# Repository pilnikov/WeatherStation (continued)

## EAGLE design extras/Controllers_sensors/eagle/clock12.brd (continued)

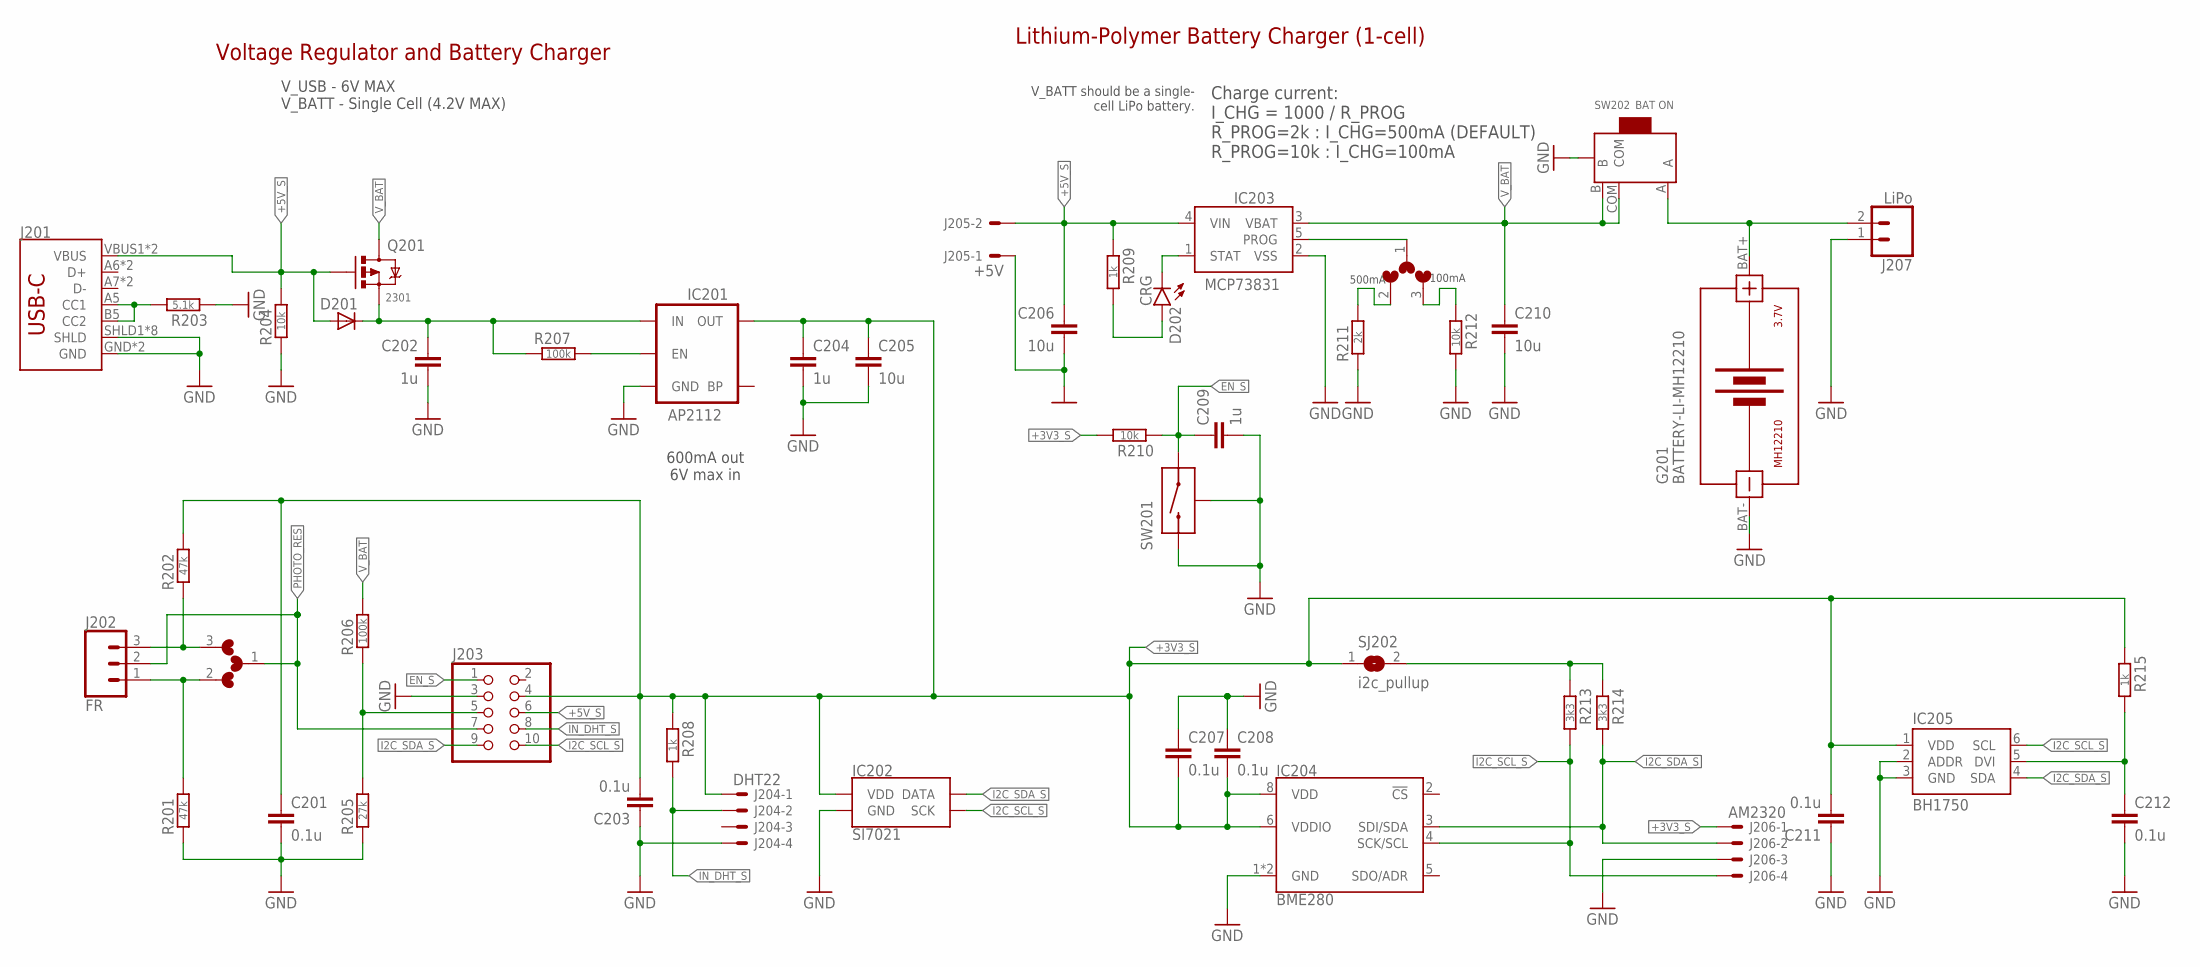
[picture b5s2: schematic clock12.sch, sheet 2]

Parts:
C201, C203, C207, C208, C211, C212: 0.1u; 0603-CAP
C202, C204, C209: 1u; 0603-CAP
C205, C206, C210: 10u; 0603-CAP
D201: 1N5819; SOD123
D202: CRG; LED-0603
G201: BATTERY-LI-MH12210
IC201: AP2112; SOT23-5
IC202: SI7021; DFN-6-3X3-SI7021
IC203: MCP73831; SOT23-5
IC204: BME280; LGA-8-2.5X2.5
IC205: BH1750; WSOF6L
J201: USB_C16PIN; USB-C-16P
J202: FR; 1X03
J203: HEADER-2X5; 2X05
J204: DHT22; 70543-04
J205: +5V; 70543-02
J206: AM2320; 70543-04
J207: LiPo; JST-2-SMD
Q201: 2301; SOT23-3@1
R201, R202: 47k; R0603
R203: 5.1k; R0603
R204, R210, R212: 10k; R0603
R205: 27k; R0603
R206, R207: 100k; R0603
R208, R209, R215: 1k; R0603
R211: 2k; R0603
R213, R214: 3k3; R0603
SJ201: PR NEG/POS; MICROBUILDER_SOLDERJUMPER_ARROW_NOPASTE_3
SJ202: i2c_pullup; MICROBUILDER_SOLDERJUMPER_ARROW_NOPASTE
SJ203: 1/5; MICROBUILDER_SOLDERJUMPER_ARROW_NOPASTE_3
SW201: MICROSWITCH-BUTTONANGLE; MICROPUSH-BUT_ANG
SW202: BAT ON; SWITCH-SMD-L6.7X2.7X3.2MM

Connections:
+3V3_S: C201.1, C203.2, C204.1, C205.1, C207.2, C208.2, C211.2, IC201.5 (OUT), IC202.VDD, IC204.6 (VDDIO), IC204.8 (VDD), IC205.1 (VDD), J203.4, J204.1, J206.1, R202.2, R208.1, R210.2, R215.1, SJ202.1
+5V: C202.1, D201.C, IC201.1 (IN), Q201.2 (S), R207.1
+5V_S: C206.1, D201.A, IC203.4 (VIN), J201.VBUS1 (VBUS), J201.VBUS2 (VBUS), J203.6, J205.2, Q201.1 (G), R204.2, R209.1
CHG: D202.C, IC203.1 (STAT)
EN_S: C209.1, J203.1, R210.1, SW201.A
EN_S_P: IC201.3 (EN), R207.2
GND: C201.2, C202.2, C203.1, C204.2, C205.2, C206.2, C207.1, C208.1, C209.2, C210.2, C211.1, C212.2, G201.BAT-, IC201.2 (GND), IC202.GND, IC203.2 (VSS), IC204.1 (GND), IC204.7 (GND), IC205.2 (ADDR), IC205.3 (GND), J201.GND, J201.GND2 (GND), J201.SHLD1 (SHLD), J201.SHLD2 (SHLD), J201.SHLD3 (SHLD), J201.SHLD4 (SHLD), J201.SHLD5 (SHLD), J201.SHLD6 (SHLD), J201.SHLD7 (SHLD), J201.SHLD8 (SHLD), J203.3, J204.4, J205.1, J206.3, J207.1 (2), R201.1, R203.1, R204.1, R205.1, R211.1, R212.2, SW201.B, SW201.SH0 (SH), SW201.SH3 (SH), SW202.SS1 (GND1), SW202.SS2 (GND1), SW202.SS3 (GND1), SW202.SS4 (GND1); also elsewhere on the board
I2C_SCL_S: IC202.SCK, IC204.4 (SCK/SCL), IC205.6 (SCL), J203.10, J206.4, R213.2
I2C_SDA_S: IC202.DATA, IC204.3 (SDI/SDA), IC205.4 (SDA), J203.9, J206.2, R214.2
IN_DHT_S: J203.8, J204.2, R208.2
unnamed: D202.A, R209.2
unnamed: R211.2, SJ203.2
unnamed: R213.1, R214.1, SJ202.2
unnamed: J203.5, R205.2, R206.1
unnamed: G201.BAT+, J207.2 (1), SW202.A
unnamed: J202.3, R202.1, SJ201.3
unnamed: IC203.5 (PROG), SJ203.1
unnamed: J202.1, R201.2, SJ201.2
unnamed: R212.1, SJ203.3
unnamed: J201.A5 (CC1), J201.B5 (CC2), R203.2
unnamed: C212.1, IC205.5 (DVI), R215.2
PHOTO_RES: J202.2, J203.7, SJ201.1
V_BAT: C210.1, IC203.3 (VBAT), Q201.3 (D), R206.2, SW202.B, SW202.COM

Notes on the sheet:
V_BATT should be a single- cell LiPo battery.
Charge current: I_CHG = 1000 / R_PROG R_PROG=2k : I_CHG=500mA (DEFAULT) R_PROG=10k : I_CHG=100mA
Voltage Regulator and Battery Charger
Lithium-Polymer Battery Charger (1-cell)
600mA out 6V max in
V_USB - 6V MAX V_BATT - Single Cell (4.2V MAX)
100mA
500mA

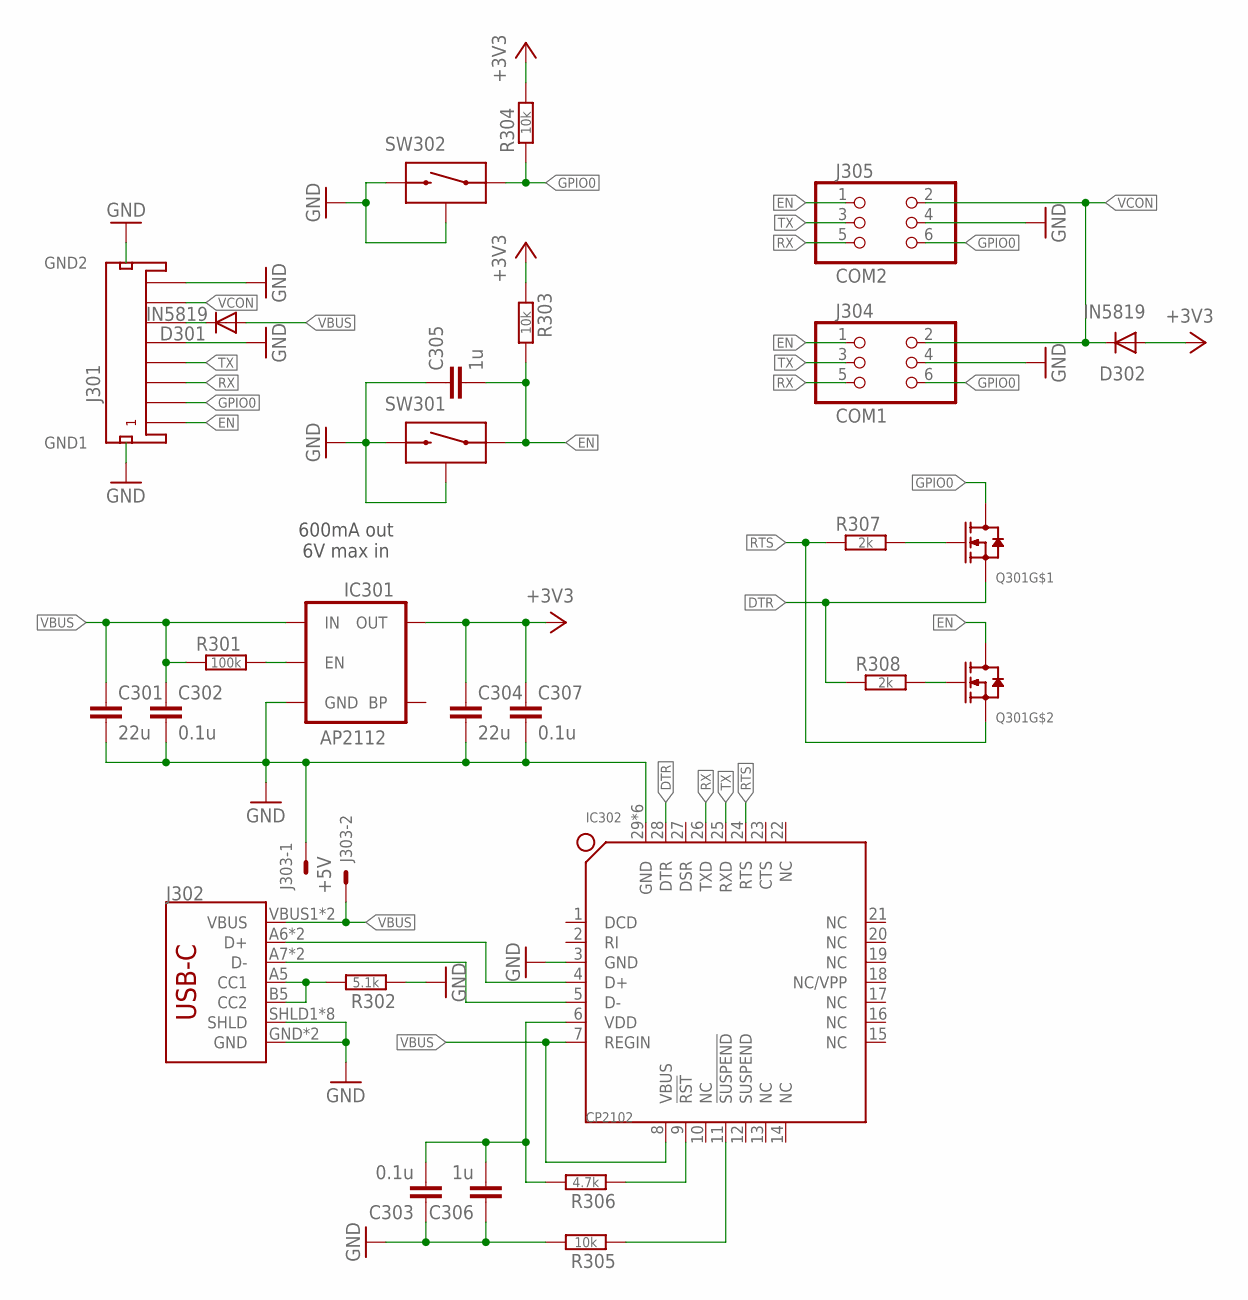
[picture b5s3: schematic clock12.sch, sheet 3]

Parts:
C301, C304: 22u; 0603-CAP
C302, C303, C307: 0.1u; 0603-CAP
C305, C306: 1u; 0603-CAP
D301, D302: IN5819; SOD123
IC301: AP2112; SOT23-5
IC302: CP2102; QFN28G_0.5-5X5MM
J301: PROG; JST-SH-8-SMT-1MM
J302: USB_C16PIN; USB-C-16P
J303: +5V; 70543-02
J304: COM1; 2X03_1.27MM_SMT
J305: COM2; 2X03_SMT
Q301: SMD-MOSFET-DUAL-N-CH-30V-2.9A-SI5902DC-T1-E3(1206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; SOT363_PHILIPS
R301: 100k; R0603
R302: 5.1k; R0603
R303, R304, R305: 10k; R0603
R306: 4.7k; R0603
R307, R308: 2k; R0603
SW301: RST; MICROPUSH-BUT_TOP
SW302: PRG; MICROPUSH-BUT_TOP

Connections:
+3V3: C304.1, C307.1, D302.A, IC301.5 (OUT), R303.1, R304.2
+3V3_CP: C303.2, C306.2, IC302.6 (VDD), R306.2
D+: IC302.4 (D+), J302.A6 (D+), J302.B6 (D+)
D-: IC302.5 (D-), J302.A7 (D-), J302.B7 (D-)
DTR: IC302.28 (DTR), Q301.1 (S), R308.1
EN: C305.2, J301.P$1 (1), J304.1, J305.1, Q301.3 (D), R303.2, SW301.A
EN_S_P1: IC301.3 (EN), R301.2
GND: C301.2, C302.2, C303.1, C304.2, C305.1, C306.1, C307.2, IC301.2 (GND), IC302.3 (GND), IC302.29 (GND), IC302.HG1 (GND), IC302.HG2 (GND), IC302.HG3 (GND), IC302.HG4 (GND), IC302.HG5 (GND), J301.P$5 (5), J301.P$8 (8), J301.P$9 (GND1), J301.P$10 (GND2), J302.GND, J302.GND2 (GND), J302.SHLD1 (SHLD), J302.SHLD2 (SHLD), J302.SHLD3 (SHLD), J302.SHLD4 (SHLD), J302.SHLD5 (SHLD), J302.SHLD6 (SHLD), J302.SHLD7 (SHLD), J302.SHLD8 (SHLD), J303.1, J304.4, J305.4, R302.1, R305.2, SW301.B, SW301.SH0 (SH), SW302.B, SW302.SH0 (SH); also elsewhere on the board
GPIO0: J301.P$2 (2), J304.6, J305.6, Q301.6 (D), R304.1, SW302.A
unnamed: D301.C, J301.P$6 (6)
unnamed: J302.A5 (CC1), J302.B5 (CC2), R302.2
unnamed: Q301.2 (G), R307.2
unnamed: Q301.5 (G), R308.2
unnamed: IC302.11 (!SUSPEND), R305.1
unnamed: IC302.9 (!RST), R306.1
RTS: IC302.24 (RTS), Q301.4 (S), R307.1
RX: IC302.26 (TXD), J301.P$3 (3), J304.5, J305.5
TX: IC302.25 (RXD), J301.P$4 (4), J304.3, J305.3
VBUS: C301.1, C302.1, D301.A, IC301.1 (IN), IC302.7 (REGIN), IC302.8 (VBUS), J302.VBUS1 (VBUS), J302.VBUS2 (VBUS), J303.2, R301.1
VCON: D302.C, J301.P$7 (7), J304.2, J305.2

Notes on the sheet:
600mA out 6V max in

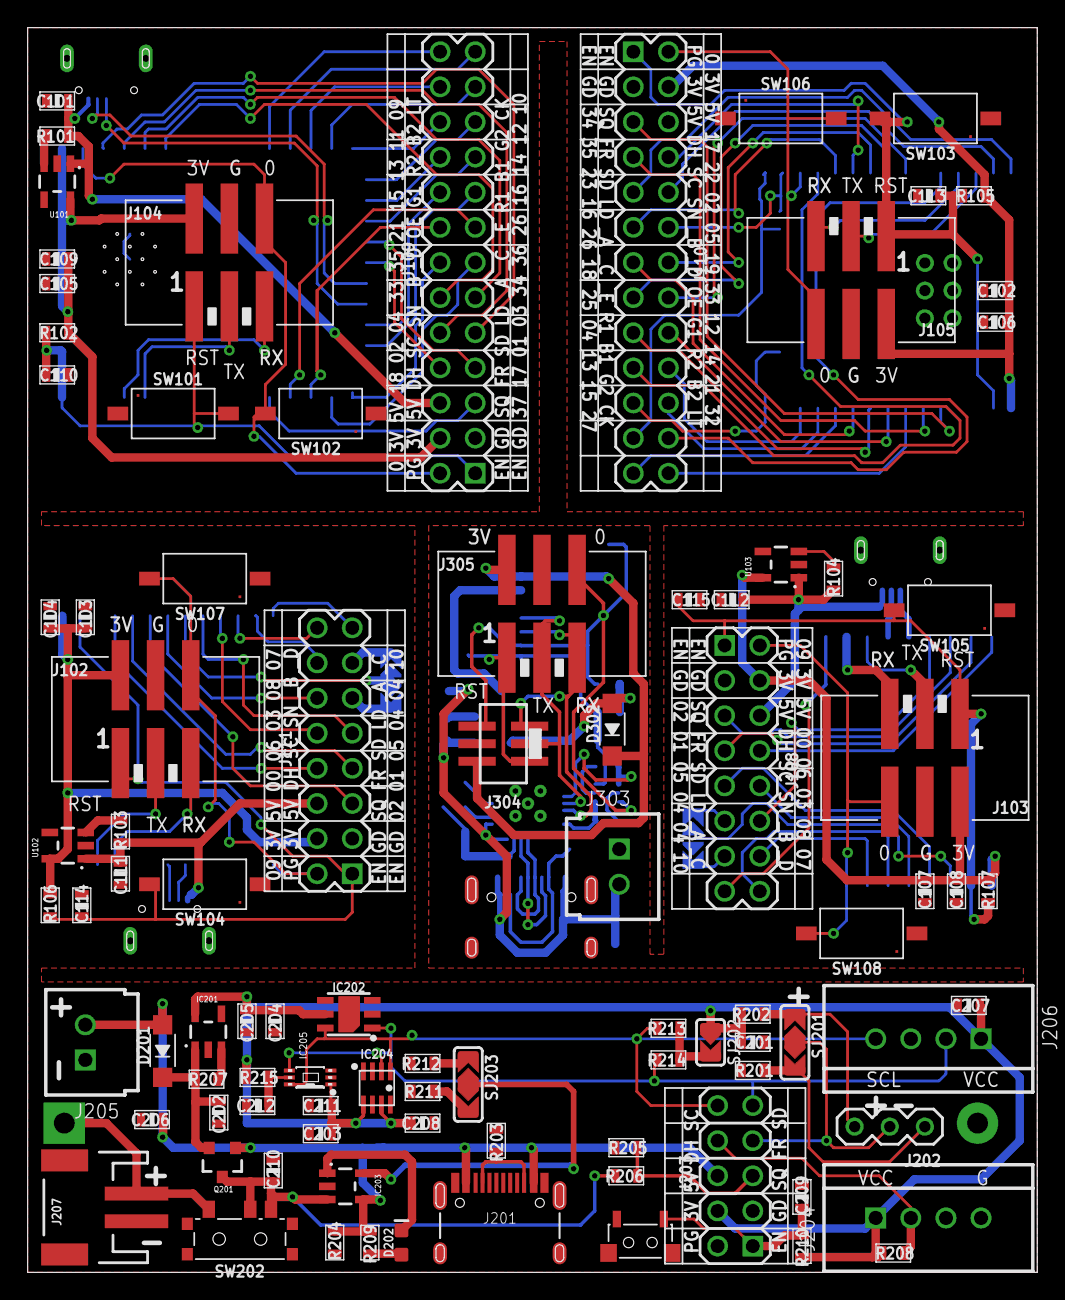
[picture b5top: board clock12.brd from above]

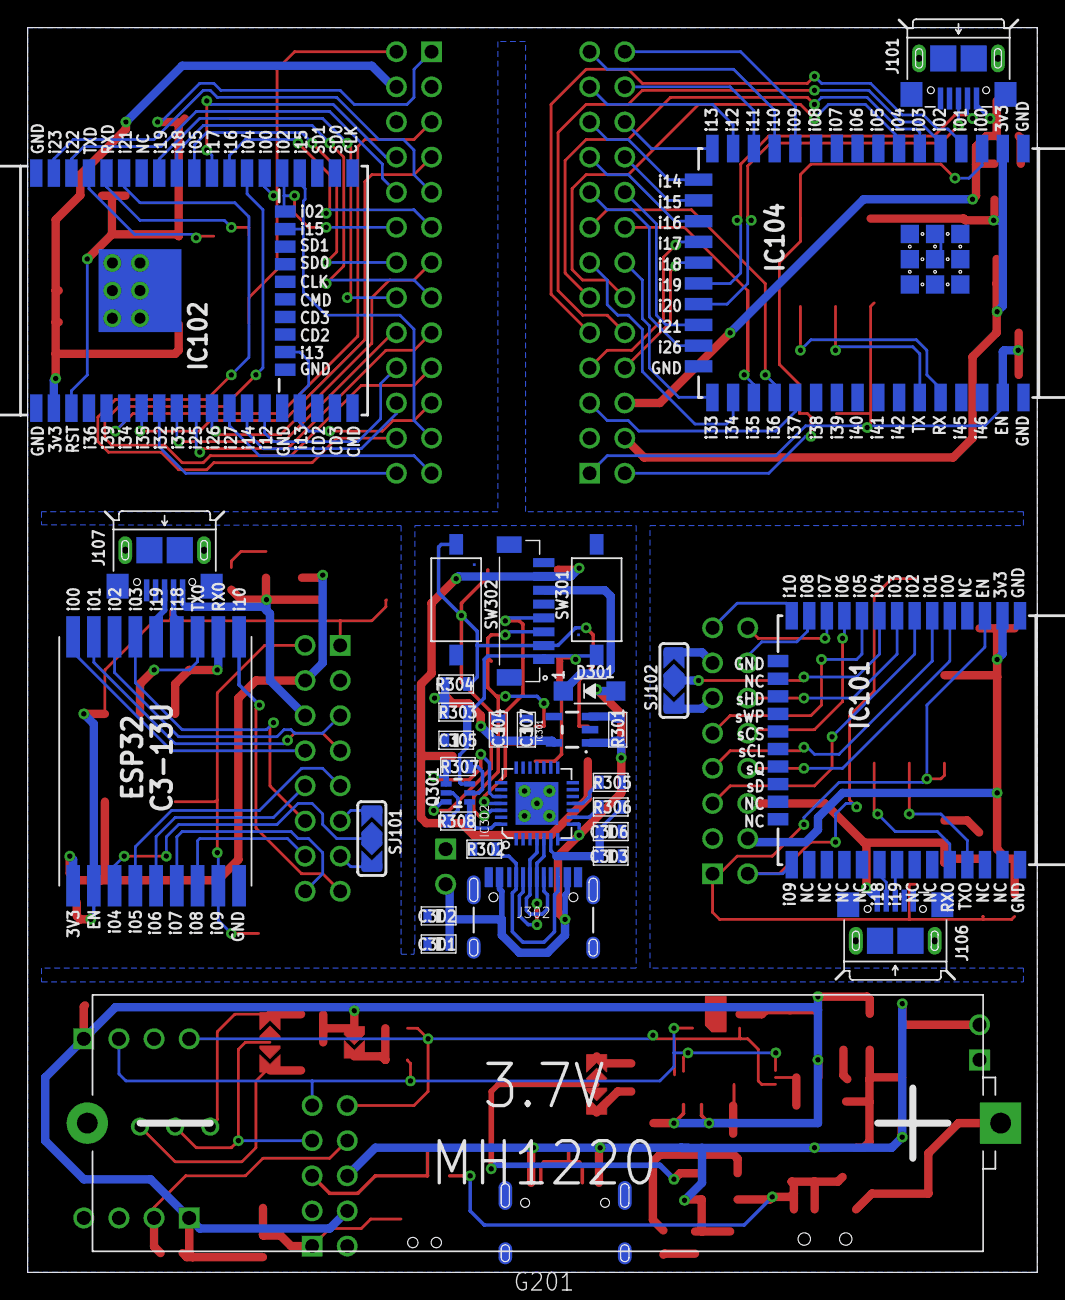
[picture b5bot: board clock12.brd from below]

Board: 2 copper layers, 73.0 x 90.0 mm, 125 parts (33 on the bottom side), 140 nets.

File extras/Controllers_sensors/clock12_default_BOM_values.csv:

Qty;Value;Device;Parts;Description;OC_FARNELL;OC_NEWARK;PROD_ID;VALUE
10;10u;CAP0603-CAP;C101, C102, C104, C105, C108, C111, C112, C205, C206, C210;Capacitor;;;;
13;0.1u;CAP0603-CAP;C103, C106, C107, C109, C201, C203, C207, C208, C211, C212, C302, C303, C307;Capacitor;;;;
9;1u;CAP0603-CAP;C110, C113, C114, C115, C202, C204, C209, C305, C306;Capacitor;;;;
2;22u;CAP0603-CAP;C301, C304;Capacitor;;;;
1;1N5819;DIODE-SOD123;D201;DIODE;;;;
1;CRG;LED-YELLOW0603;D202;Yellow SMD LED;;;DIO-09003;Yellow
2;IN5819;DIODE-SOD123;D301, D302;DIODE;;;;
1;BATTERY-LI-MH12210;BATTERY-LI-MH12210;G201;Lithium-Ion MH12210 Rechargeable Battery;;;;
1;ESP32C3;ESP32C3-MODULE32S;IC101;;;;;
1;ESP32;ESP32-MODULEDUAL;IC102;;;;;
1;ESP32C3-MODULE13U;ESP32C3-MODULE13U;IC103;;;;;
1;ESP32S2;ESP32S2-MODULEAI;IC104;;;;;
5;AP2112;V_REG_LDOSMD;IC201, IC301, U101, U102, U103;Voltage Regulator LDO;;;VREG-12457;
1;SI7021;SI7021;IC202;Silicon Labs Si7021 I2C Humidity and Temperature Sensor;;;IC-13093;
1;MCP73831;MCP73831;IC203;Miniature single cell, fully integrated Li-Ion, Li-polymer charge management controller;;;IC-09995;
1;BME280;BME280;IC204;"Bosch BME280 &ndash; Combined Humidity and Pressure Sensor";;;IC-13090;BME280
1;BH1750;BH1750;IC205;;;;IC-13876;ZOPT2201
1;CP2102;CP2102-GMR(QFN28);IC302;310070003;;;;CP2102-GMR-QFN28
3;;USB_MICRO-BFEMALE_SMT_;J101, J106, J107;USB Type Micro-B Connector;;;;
4;COM;HEADER-2X3SMT;J102, J103, J104, J105;PIN HEADER;;;;
2;;HEADER-2X8;J108, J111;PIN HEADER;;;;
2;;HEADER-2X13;J109, J110;PIN HEADER;;;;
2;;USB_C16PIN;J201, J302;USB Type C 16Pin Connector;;;CONN-14122;
1;FR;CONN_03;J202;Multi connection point. Often used as Generic Header-pin footprint for 0.1 inch spaced/style header connections;;;XXX-00000;455-1750-1-ND
1;;HEADER-2X5;J203;PIN HEADER;;;;
1;DHT22;C-GRID-04-70543;J204;CONNECTOR;unknown;unknown;;
2;+5V;C-GRID-02-70543;J205, J303;CONNECTOR;unknown;unknown;;
1;AM2320;C-GRID-04-70543;J206;CONNECTOR;unknown;unknown;;
1;LiPo;CONN_02-JST-2MM-SMT;J207;Multi connection point. Often used as Generic Header-pin footprint for 0.1 inch spaced/style header connections;;;CONN-11443;
1;PROG;JST-SH-1MM-8;J301;;;;;
1;COM1;HEADER-2X3SMT_1.27;J304;PIN HEADER;;;;
1;COM2;HEADER-2X3SMT;J305;PIN HEADER;;;;
1;2301;MOSFET-PCHANNELDMG2307L;Q201;Generic PMOSFET;;;TRANS-11308;2.5A/30V
1;;SMD-MOSFET-DUAL-N-CH-30V-2.9A-SI5902DC-T1-E3(1206-8)SOT363;Q301;305040005;;;;
6;100k;R-EU_R0603;R101, R103, R104, R206, R207, R301;RESISTOR, European symbol;;;;
10;10k;R-EU_R0603;R102, R105, R106, R107, R204, R210, R212, R303, R304, R305;RESISTOR, European symbol;;;;
2;47k;R-EU_R0603;R201, R202;RESISTOR, European symbol;;;;
2;5.1k;R-EU_R0603;R203, R302;RESISTOR, European symbol;;;;
1;27k;R-EU_R0603;R205;RESISTOR, European symbol;;;;
3;1k;R-EU_R0603;R208, R209, R215;RESISTOR, European symbol;;;;
3;2k;R-EU_R0603;R211, R307, R308;RESISTOR, European symbol;;;;
2;3k3;R-EU_R0603;R213, R214;RESISTOR, European symbol;;;;
1;4.7k;R-EU_R0603;R306;RESISTOR, European symbol;;;;
5;RST;MICROSWITCH-BUTTON;SW101, SW103, SW104, SW105, SW301;;;;;
5;PRG;MICROSWITCH-BUTTON;SW102, SW106, SW107, SW108, SW302;;;;;
1;MICROSWITCH-BUTTONANGLE;MICROSWITCH-BUTTONANGLE;SW201;;;;;
1;BAT ON;SMD-TOGGLE-SWITCH-ON-ON(3+4P-6.7X2.7MM)ORIG;SW202;311030001;;;;

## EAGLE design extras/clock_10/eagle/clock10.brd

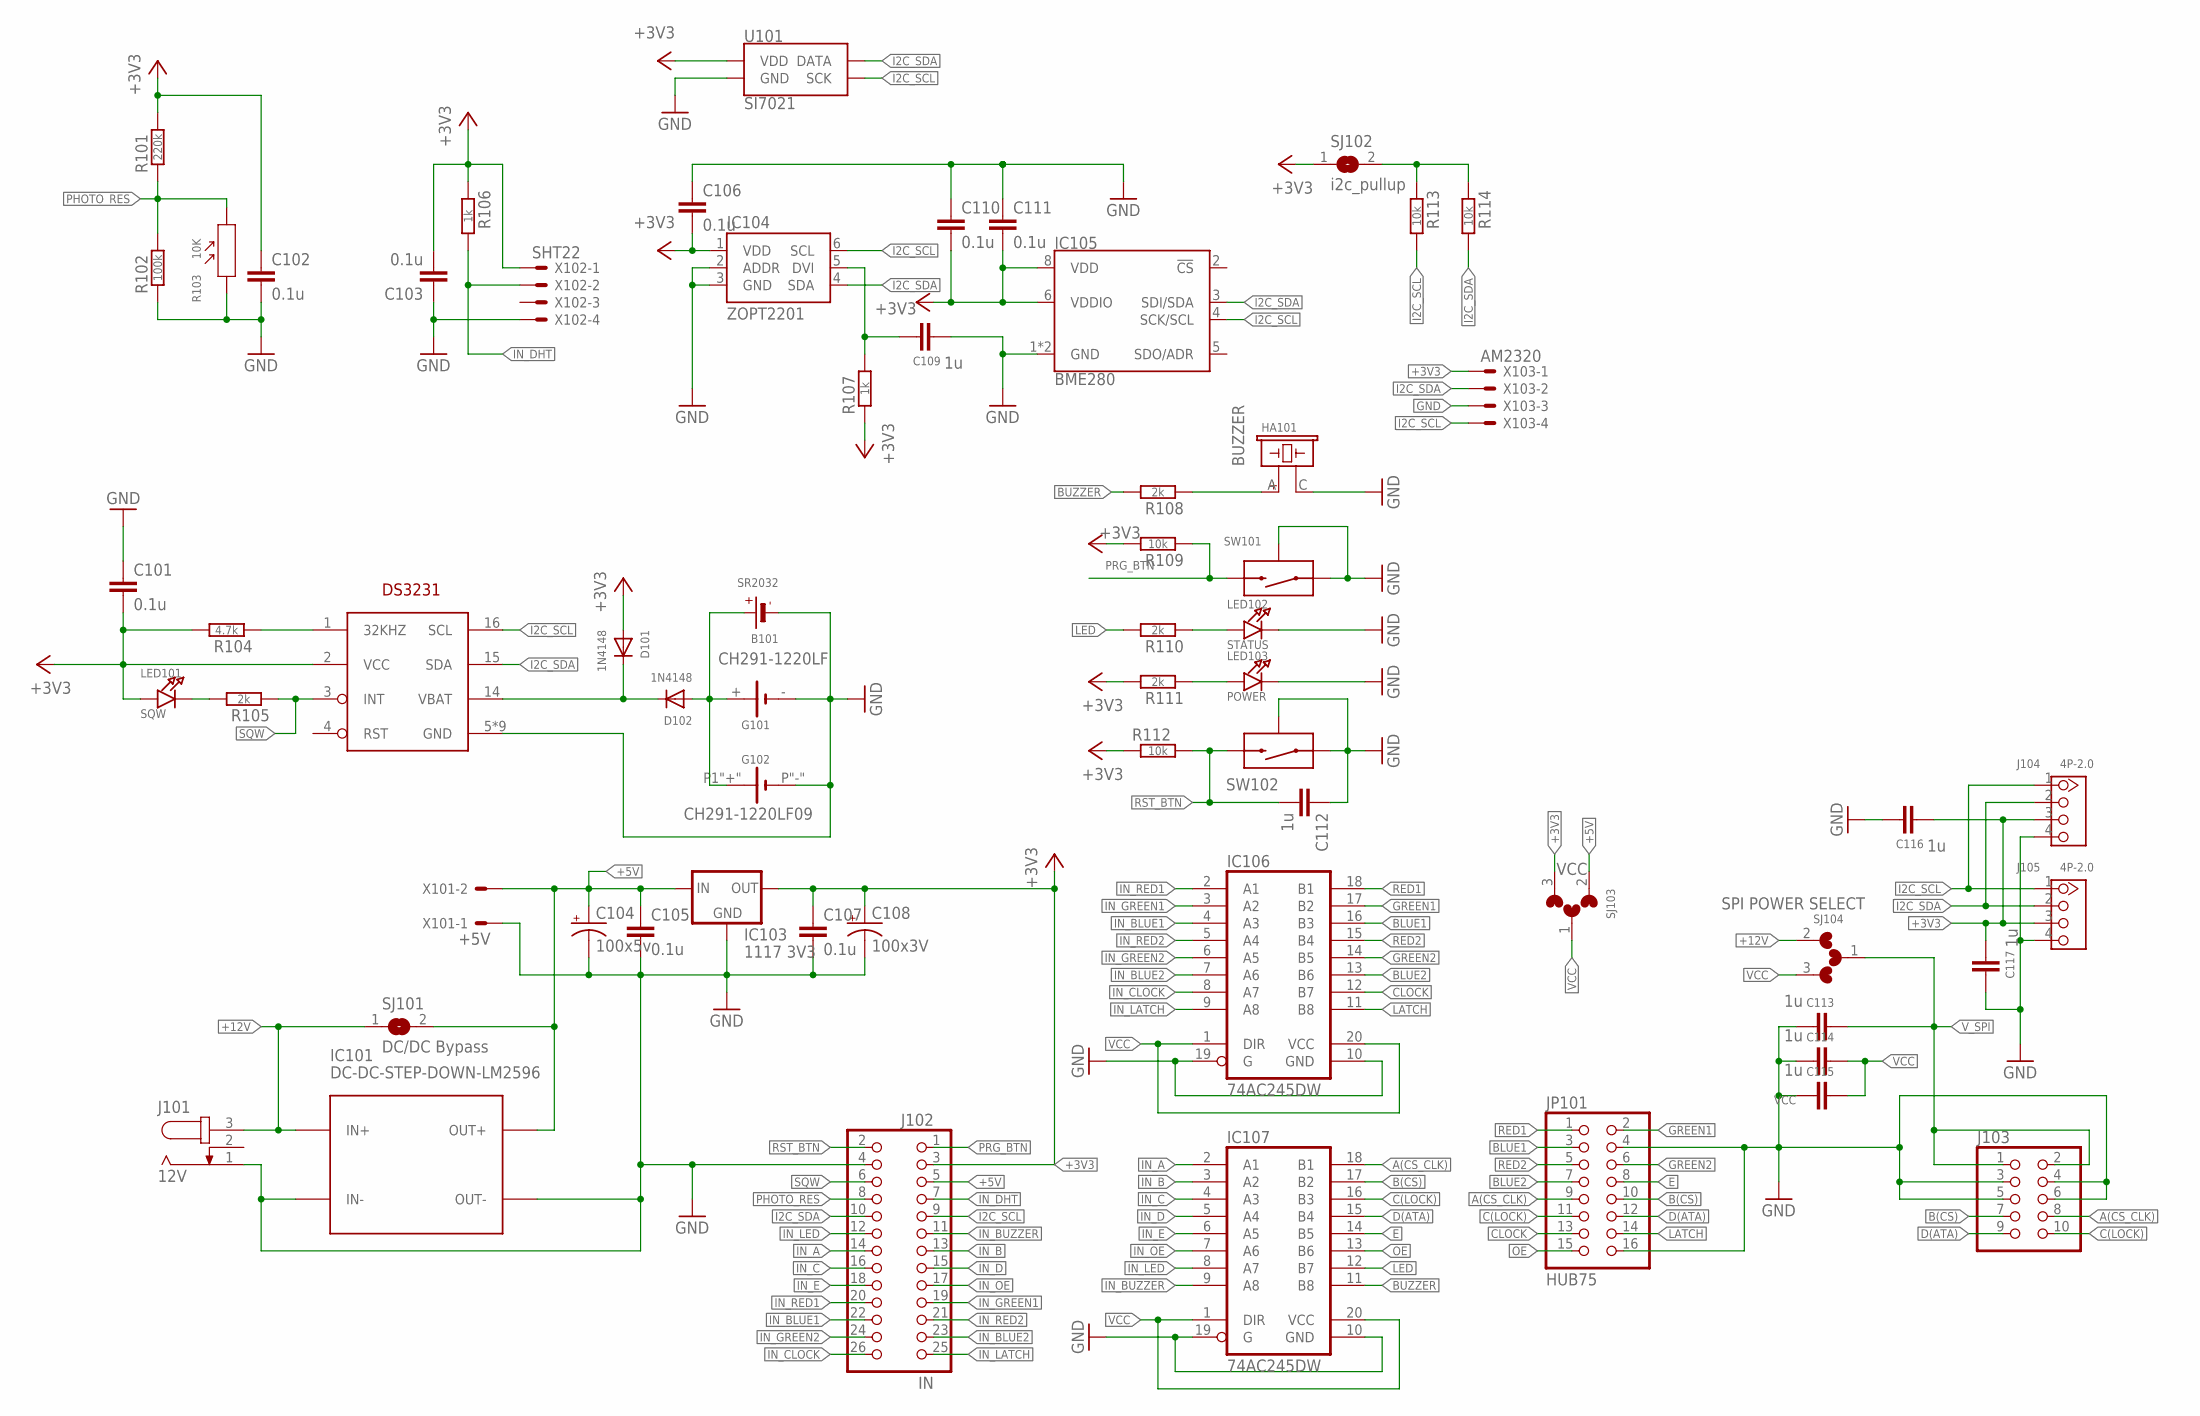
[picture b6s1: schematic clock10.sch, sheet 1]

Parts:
B101: SR2032; CR2032
C101, C102, C103, C105, C106, C107, C110, C111: 0.1u; 0603-CAP
C104: 100x5v; CPOL-RADIAL-100UF-25V
C108: 100x3V; CPOL-RADIAL-100UF-25V
C109, C112, C113, C114, C115, C116, C117: 1u; 0603-CAP
D101, D102: 1N4148; SOD-323F
G101: CH291-1220LF
G102: CH291-1220LF09; CH23-09LF
HA101: BUZZER; PBUZ_12X7.5
IC101: DC-DC-STEP-DOWN-LM2596
IC102: DS3231W; SO16W
IC103: 1117 3V3; SOT223
IC104: ZOPT2201; WSOF6L
IC105: BME280; LGA-8-2.5X2.5
IC106, IC107: 74AC245DW; SO20W
J101: 12V; SPC4077
J102: IN; 2X13
J103: HEADER-2X5IDC; 2X05_IDC
J104, J105: 4P-2.0; HW4-2.0
JP101: HUB75; 2X08
LED101: SQW; CHIPLED_0603
LED102: STATUS; CHIPLED_0603
LED103: POWER; CHIPLED_0603
R101: 220k; R0603
R102: 100k; R0603
R103: 10K; SNR2-3.0
R104: 4.7k; R0603
R105, R108, R110, R111: 2k; R0603
R106, R107: 1k; R0603
R109, R112, R113, R114: 10k; R0603
SJ101: DC/DC Bypass; MICROBUILDER_SOLDERJUMPER_ARROW_NOPASTE
SJ102: i2c_pullup; MICROBUILDER_SOLDERJUMPER_ARROW_NOPASTE
SJ103: VCC; MICROBUILDER_SOLDERJUMPER_ARROW_NOPASTE_3
SJ104: SPI POWER SELECT; MICROBUILDER_SOLDERJUMPER_ARROW_NOPASTE_3
SW101: PRG; MICROPUSH-BUT_TOP
SW102: RST; MICROPUSH-BUT_TOP
U101: SI7021; DFN-6-3X3-SI7021
X101: +5V; 70543-02
X102: SHT22; 70543-04
X103: AM2320; 70543-04

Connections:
+3V3: C101.2, C102.1, C103.2, C106.2, C107.1, C108.1 (+), C110.2, C111.2, C116.2, C117.2, D101.A, IC102.2 (VCC), IC103.2 (OUT), IC103.4 (OUT), IC104.1 (VDD), IC105.6 (VDDIO), IC105.8 (VDD), J102.3, J104.3, J105.3, LED101.A, R101.2, R104.2, R106.1, R107.1, R109.2, R111.2, R112.1, SJ102.1, SJ103.3, U101.VDD, X102.1, X103.1
+5V: C104.1 (+), C105.1, IC101.OUT+, IC103.3 (IN), J102.5, SJ101.2, SJ103.2, X101.2
+12V: IC101.IN+, J101.3, SJ101.1, SJ104.2
A(CS_CLK): IC107.18 (B1), J103.8, JP101.9
B(CS): IC107.17 (B2), J103.7, JP101.10
BLUE1: IC106.16 (B3), JP101.3
BLUE2: IC106.13 (B6), JP101.7
BUZ: HA101.A, R108.1
BUZZER: IC107.11 (B8), R108.2
C(LOCK): IC107.16 (B3), J103.10, JP101.11
CLOCK: IC106.12 (B7), JP101.13
D(ATA): IC107.15 (B4), J103.9, JP101.12
E: IC107.14 (B5), JP101.8
GND: B101.-, C101.1, C102.2, C103.1, C104.2 (-), C105.2, C106.1, C107.2, C108.2 (-), C109.2, C110.1, C111.1, C112.1, C113.2, C114.2, C115.2, C116.1, C117.1, G101.-, G102.P"-" (-), HA101.C, IC101.IN-, IC101.OUT-, IC102.5 (GND), IC102.6 (GND), IC102.7 (GND), IC102.8 (GND), IC102.9 (GND), IC102.10 (GND), IC102.11 (GND), IC102.12 (GND), IC102.13 (GND), IC103.1 (GND), IC104.2 (ADDR), IC104.3 (GND), IC105.1 (GND), IC105.7 (GND), IC106.10 (GND), IC106.19 (G), IC107.10 (GND), IC107.19 (G), J101.1, J102.4, J103.3, J103.4, J103.5, J103.6, J104.4, J105.4, JP101.4, JP101.16, LED102.C, LED103.C, R102.1, R103.1, SW101.A, SW101.SH0 (SH), SW102.A, SW102.SH0 (SH), U101.GND, X101.1, X102.4, X103.3; also elsewhere on the board
GREEN1: IC106.17 (B2), JP101.2
GREEN2: IC106.14 (B5), JP101.6
I2C_SCL: IC102.16 (SCL), IC104.6 (SCL), IC105.4 (SCK/SCL), J102.9, J104.1, J105.1, R113.2, U101.SCK, X103.4
I2C_SDA: IC102.15 (SDA), IC104.4 (SDA), IC105.3 (SDI/SDA), J102.10, J104.2, J105.2, R114.2, U101.DATA, X103.2
IN_A: IC107.2 (A1), J102.14
IN_B: IC107.3 (A2), J102.13
IN_BLUE1: IC106.4 (A3), J102.22
IN_BLUE2: IC106.7 (A6), J102.23
IN_BUZZER: IC107.9 (A8), J102.11
IN_C: IC107.4 (A3), J102.16
IN_CLOCK: IC106.8 (A7), J102.26
IN_D: IC107.5 (A4), J102.15
IN_DHT: J102.7, R106.2, X102.2
IN_E: IC107.6 (A5), J102.18
IN_GREEN1: IC106.3 (A2), J102.19
IN_GREEN2: IC106.6 (A5), J102.24
IN_LATCH: IC106.9 (A8), J102.25
IN_LED: IC107.8 (A7), J102.12
IN_OE: IC107.7 (A6), J102.17
IN_RED1: IC106.2 (A1), J102.20
IN_RED2: IC106.5 (A4), J102.21
LATCH: IC106.11 (B8), JP101.14
LED: IC107.12 (B7), R110.2
unnamed: D101.C, D102.C, IC102.14 (VBAT)
unnamed: LED103.A, R111.1
unnamed: LED102.A, R110.1
unnamed: LED101.C, R105.2
unnamed: C109.1, IC104.5 (DVI), R107.2
unnamed: IC102.1 (32KHZ), R104.1
unnamed: R113.1, R114.1, SJ102.2
unnamed: B101.+, D102.A, G101.+, G102.P1"+" (+)
OE: IC107.13 (B6), JP101.15
PHOTO_RES: J102.8, R101.1, R102.2, R103.2
PRG_BTN: J102.1, R109.1, SW101.B
RED1: IC106.18 (B1), JP101.1
RED2: IC106.15 (B4), JP101.5
RST_BTN: C112.2, J102.2, R112.2, SW102.B
SQW: IC102.3 (INT), J102.6, R105.1
VCC: C114.1, C115.1, IC106.1 (DIR), IC106.20 (VCC), IC107.1 (DIR), IC107.20 (VCC), SJ103.1, SJ104.3
V_SPI: C113.1, J103.1, J103.2, SJ104.1

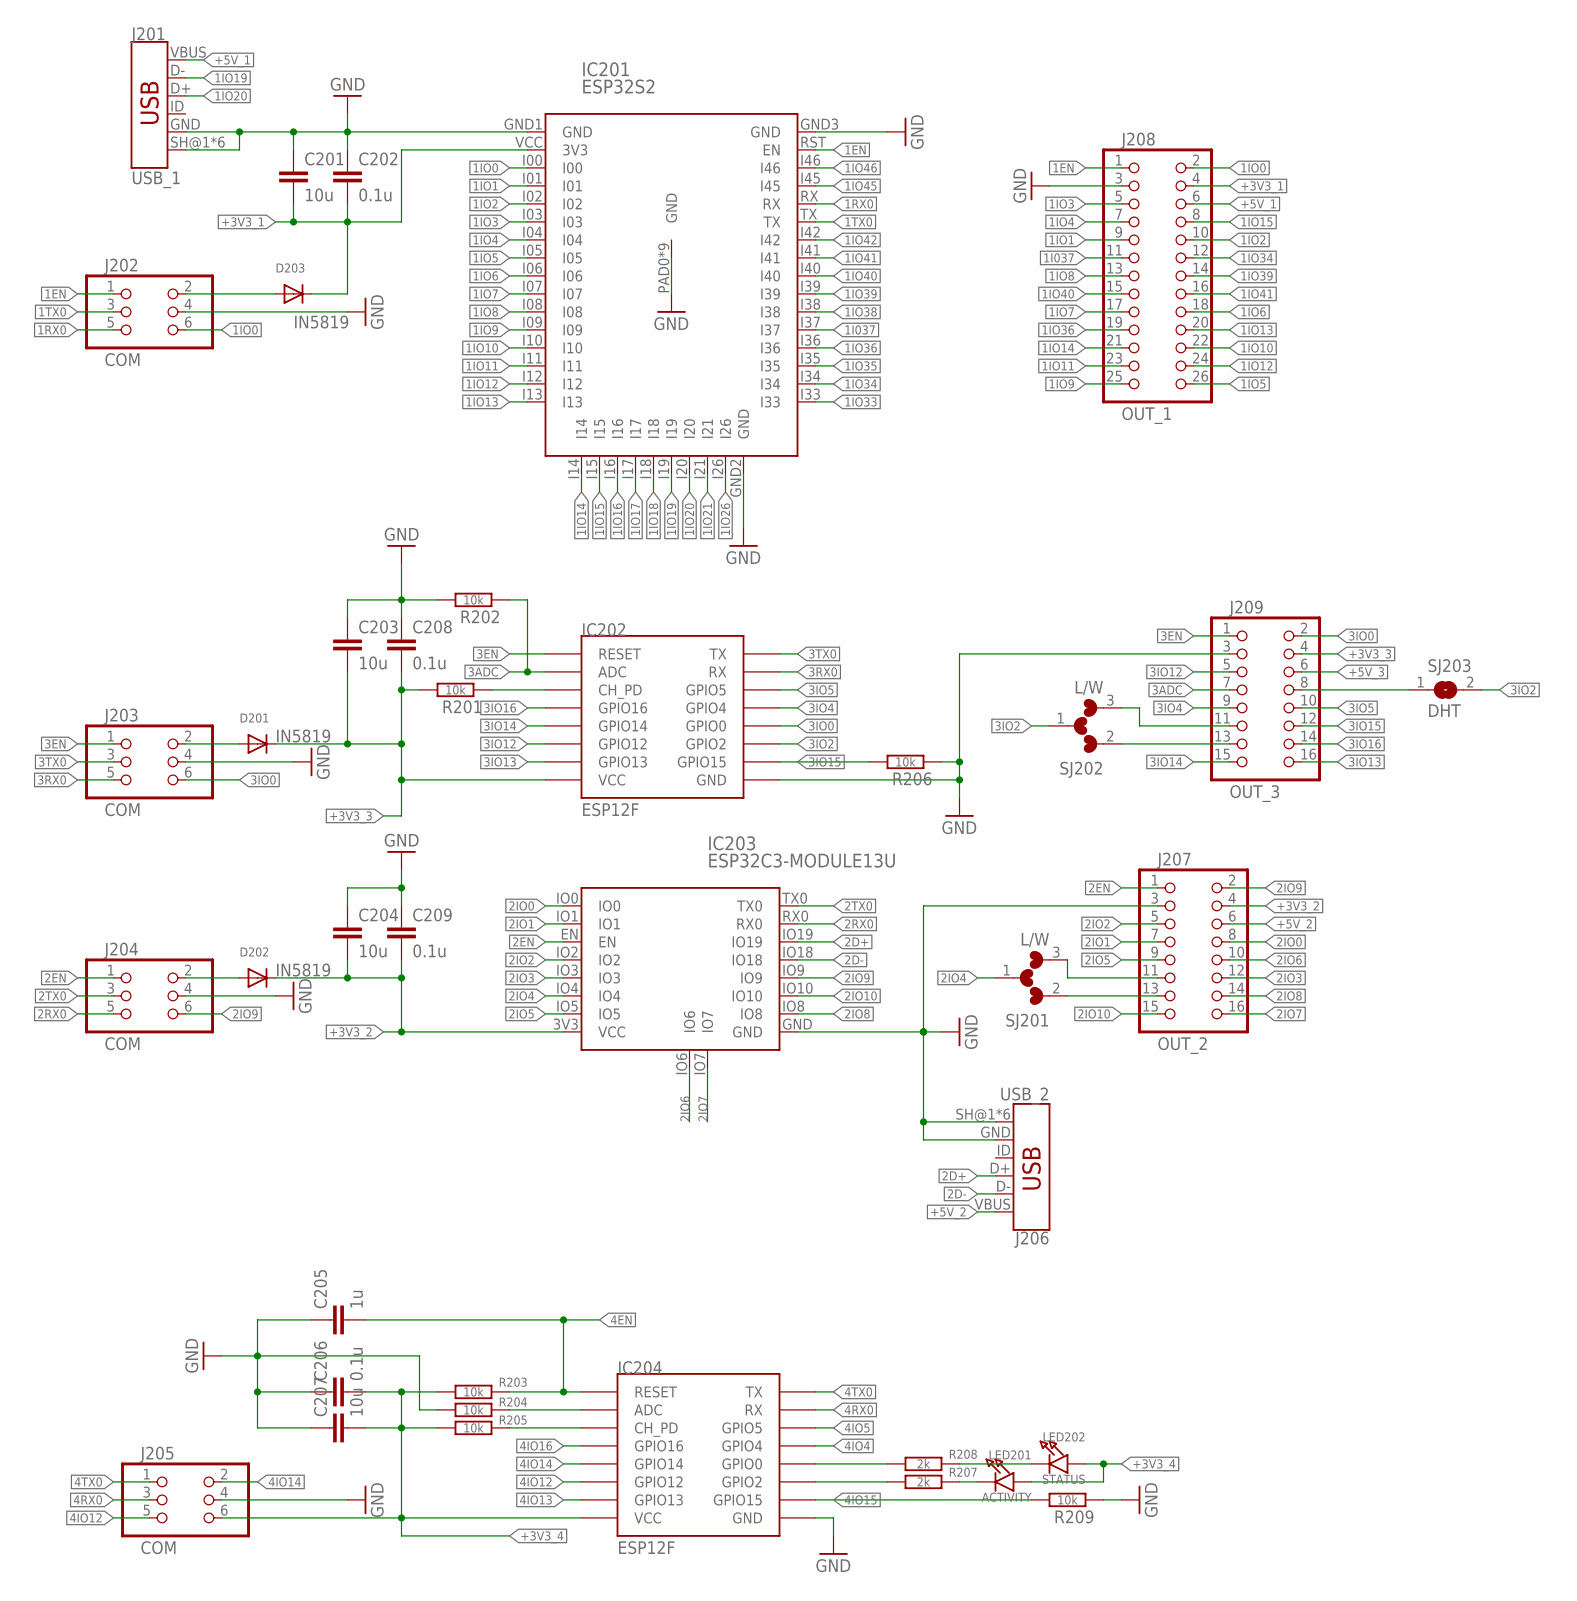
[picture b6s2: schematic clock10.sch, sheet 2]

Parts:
C201, C203, C204, C207: 10u; 0603-CAP
C202, C206, C208, C209: 0.1u; 0603-CAP
C205: 1u; 0603-CAP
D201, D202, D203: IN5819; SOD123
IC201: ESP32S2; ESP-12K
IC202, IC204: ESP12F; ESP12-SMD
IC203: ESP32C3-MODULE13U; ESP32C3-13U
J201: USB_1; USB-B-MICRO-SMD_MY
J202, J203, J204, J205: COM; 2X03_SMT
J206: USB_2; USB-B-MICRO-SMD_MY
J207: OUT_2; 2X8
J208: OUT_1; 2X13
J209: OUT_3; 2X8
LED201: ACTIVITY; CHIPLED_0603
LED202: STATUS; CHIPLED_0603
R201, R202, R203, R204, R205, R206, R209: 10k; R0603
R207, R208: 2k; R0603
SJ201, SJ202: L/W; MICROBUILDER_SOLDERJUMPER_ARROW_NOPASTE_3
SJ203: DHT; MICROBUILDER_SOLDERJUMPER_ARROW_NOPASTE

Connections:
1EN: IC201.RST (EN), J202.1, J208.1
1I037: IC201.I37, J208.11
1IO0: IC201.I00, J202.6, J208.2
1IO1: IC201.I01, J208.9
1IO2: IC201.I02, J208.10
1IO3: IC201.I03, J208.5
1IO4: IC201.I04, J208.7
1IO5: IC201.I05, J208.26
1IO6: IC201.I06, J208.18
1IO7: IC201.I07, J208.17
1IO8: IC201.I08, J208.13
1IO9: IC201.I09, J208.25
1IO10: IC201.I10, J208.22
1IO11: IC201.I11, J208.23
1IO12: IC201.I12, J208.24
1IO13: IC201.I13, J208.20
1IO14: IC201.I14, J208.21
1IO15: IC201.I15, J208.8
1IO16: IC201.I16
1IO17: IC201.I17
1IO18: IC201.I18
1IO19: IC201.I19, J201.D-
1IO20: IC201.I20, J201.D+
1IO21: IC201.I21
1IO26: IC201.I26
1IO33: IC201.I33
1IO34: IC201.I34, J208.12
1IO35: IC201.I35
1IO36: IC201.I36, J208.19
1IO38: IC201.I38
1IO39: IC201.I39, J208.14
1IO40: IC201.I40, J208.15
1IO41: IC201.I41, J208.16
1IO42: IC201.I42
1IO45: IC201.I45
1IO46: IC201.I46
1RX0: IC201.RX, J202.5
1TX0: IC201.TX, J202.3
2D+: IC203.IO19, J206.D+
2D-: IC203.IO18, J206.D-
2EN: IC203.EN, J204.1, J207.1
2IO0: IC203.IO0, J207.8
2IO1: IC203.IO1, J207.7
2IO2: IC203.IO2, J207.5
2IO3: IC203.IO3, J207.12
2IO4: IC203.IO4, SJ201.1
2IO5: IC203.IO5, J207.9
2IO6: IC203.IO6, J207.10
2IO7: IC203.IO7, J207.16
2IO8: IC203.IO8, J207.14
2IO9: IC203.IO9, J204.6, J207.2
2IO10: IC203.IO10, J207.15
2RX0: IC203.RX0, J204.5
2TX0: IC203.TX0, J204.3
3ADC: IC202.ADC, J209.7, R202.1
3EN: IC202.RESET, J203.1, J209.1
3IO0: IC202.GPIO0, J203.6, J209.2
3IO2: IC202.GPIO2, SJ202.1, SJ203.2
3IO4: IC202.GPIO4, J209.9
3IO5: IC202.GPIO5, J209.10
3IO12: IC202.GPIO12, J209.5
3IO13: IC202.GPIO13, J209.16
3IO14: IC202.GPIO14, J209.15
3IO15: IC202.GPIO15, J209.12, R206.2
3IO16: IC202.GPIO16, J209.14
3RX0: IC202.RXD0 (RX), J203.5
3TX0: IC202.TXD0 (TX), J203.3
4EN: C205.2, IC204.RESET, R203.1
4IO0: IC204.GPIO0, R208.1
4IO2: IC204.GPIO2, R207.1
4IO4: IC204.GPIO4
4IO5: IC204.GPIO5
4IO12: IC204.GPIO12, J205.5
4IO13: IC204.GPIO13
4IO14: IC204.GPIO14, J205.2
4IO15: IC204.GPIO15, R209.2
4IO16: IC204.GPIO16
4RX0: IC204.RXD0 (RX), J205.3
4TX0: IC204.TXD0 (TX), J205.1
+3V3_1: C201.2, C202.2, D203.C, IC201.VCC (3V3), J208.4
+3V3_2: C204.2, C209.2, D202.C, IC203.3V3 (VCC), J207.4
+3V3_3: C203.2, C208.2, D201.C, IC202.VCC, J209.4, R201.2
+3V3_4: C206.2, C207.2, IC204.VCC, J205.6, LED201.A, LED202.A, R203.2, R205.2
+5V_1: J201.VBUS, J208.6
+5V_2: J206.VBUS, J207.6
+5V_3: J209.6
COM_VCC2: D201.A, J203.2
GND: C201.1, C202.1, C203.1, C204.1, C205.1, C206.1, C207.1, C208.1, C209.1, IC201.GND1 (GND), IC201.GND2 (GND), IC201.GND3 (GND), IC201.PAD0 (GND), IC201.PAD1 (GND), IC201.PAD2 (GND), IC201.PAD3 (GND), IC201.PAD4 (GND), IC201.PAD5 (GND), IC201.PAD6 (GND), IC201.PAD7 (GND), IC201.PAD8 (GND), IC202.GND, IC203.GND, IC204.GND, J201.GND, J201.SH@1 (SHIELD), J201.SH@2 (SHIELD), J201.SH@3 (SHIELD), J201.SH@4 (SHIELD), J201.SH@5 (SHIELD), J201.SH@6 (SHIELD), J202.4, J203.4, J204.4, J205.4, J206.GND, J206.SH@1 (SHIELD), J206.SH@2 (SHIELD), J206.SH@3 (SHIELD), J206.SH@4 (SHIELD), J206.SH@5 (SHIELD), J206.SH@6 (SHIELD), J207.3, J208.3, J209.3, R202.2, R204.2, R206.1, R209.1; also elsewhere on the board
IN2_A: J207.13, SJ201.2
IN3_DHT: J209.8, SJ203.1
unnamed: D203.A, J202.2
unnamed: IC202.CH_PD, R201.1
unnamed: D202.A, J204.2
unnamed: IC204.CH_PD, R205.1
unnamed: IC204.ADC, R204.1
unnamed: LED202.C, R208.2
unnamed: LED201.C, R207.2
unnamed: J209.13, SJ202.2
unnamed: J209.11, SJ202.3
unnamed: J207.11, SJ201.3
